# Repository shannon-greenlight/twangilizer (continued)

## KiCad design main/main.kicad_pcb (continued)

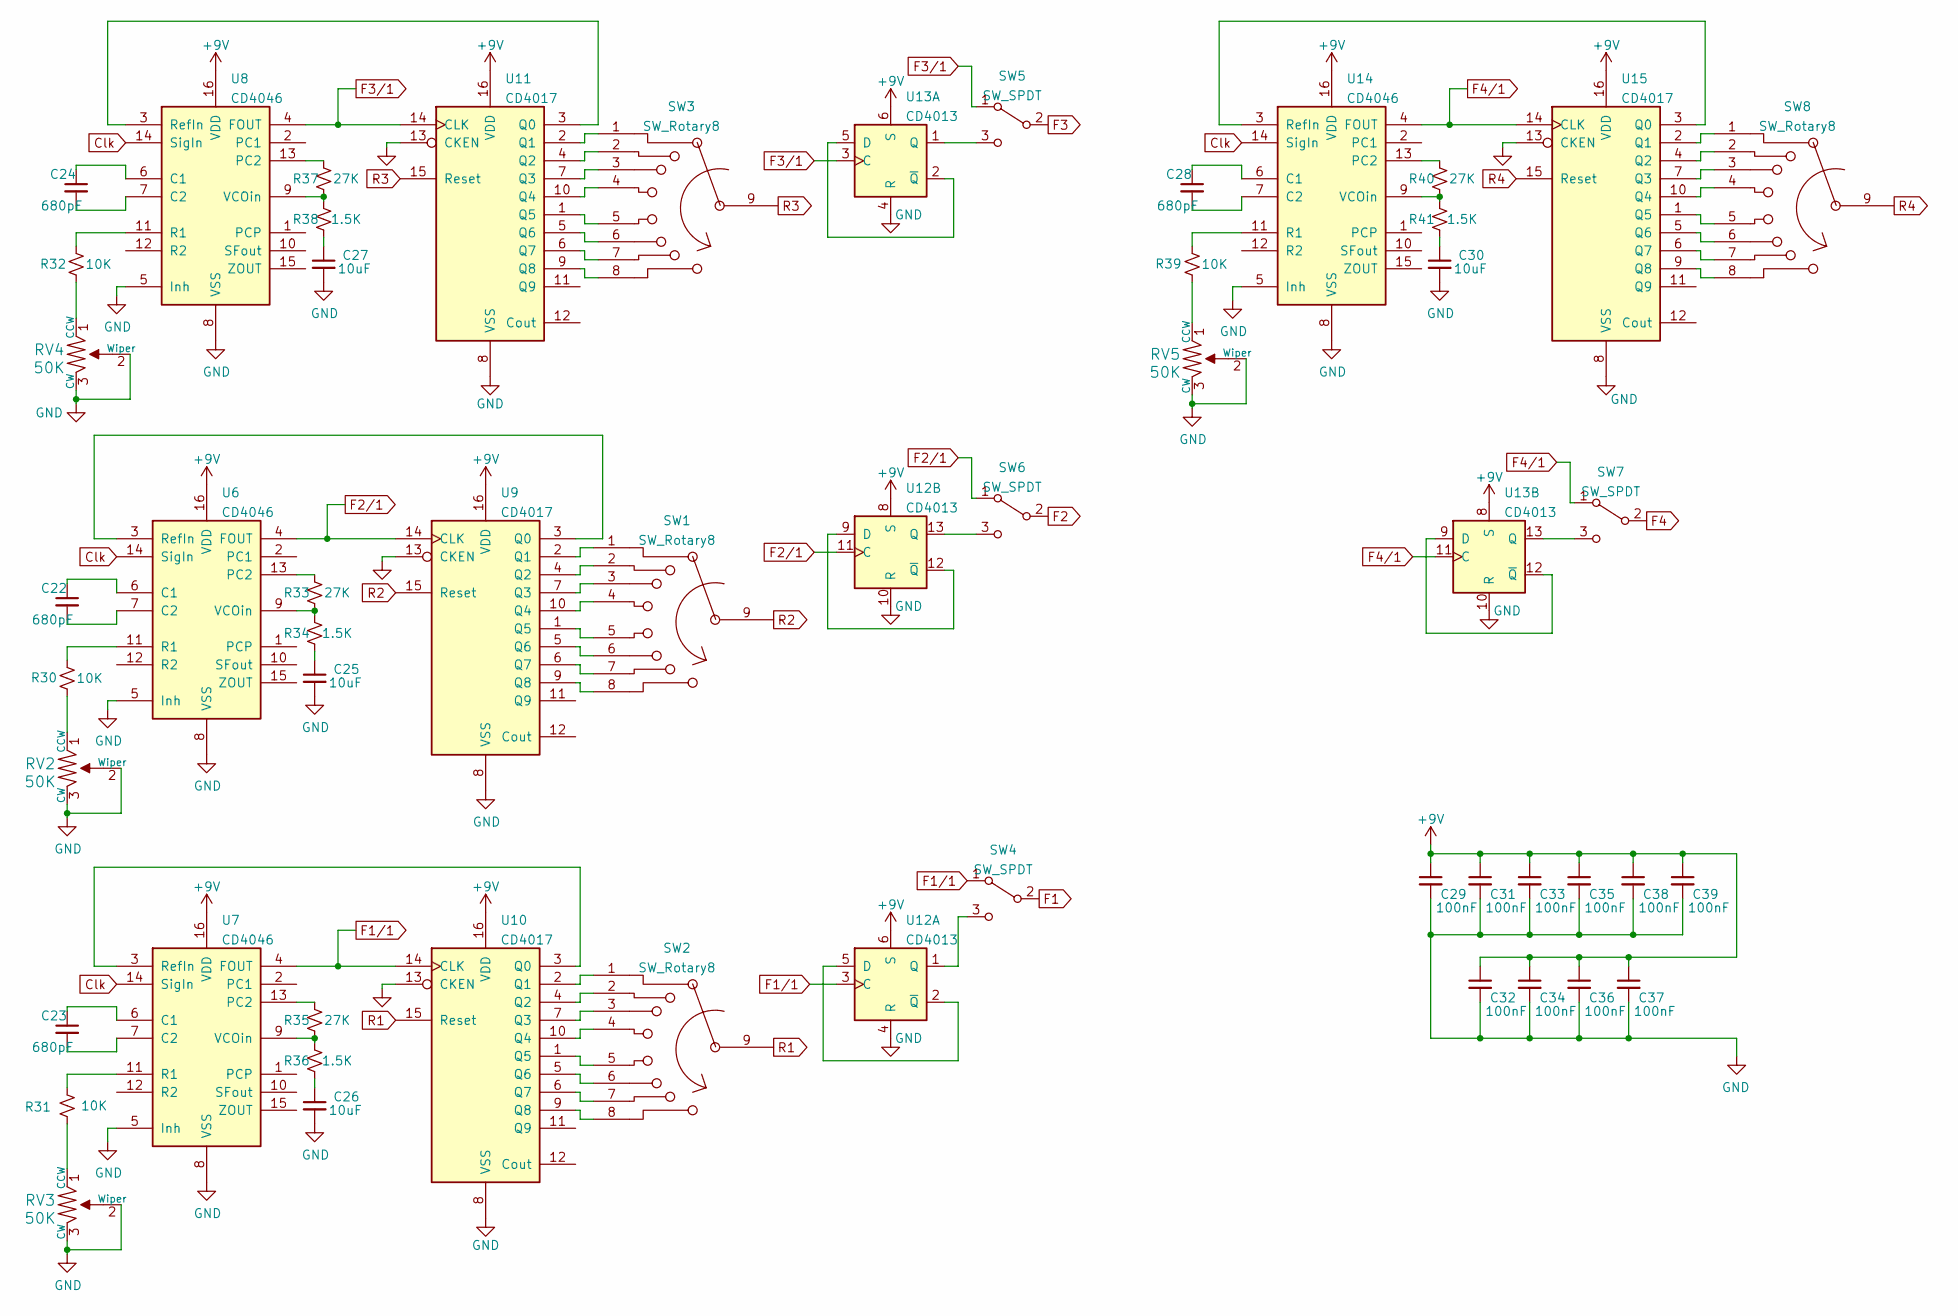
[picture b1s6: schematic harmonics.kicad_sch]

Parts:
C22, C23, C24, C28: 680pF; C_0805_2012Metric_Pad1.18x1.45mm_HandSolder; Digi-Key Part BC2662CT-ND
C25, C26, C27, C30: 10uF; C_0805_2012Metric_Pad1.18x1.45mm_HandSolder; Digi-Key Part 478-10836-1-ND
C29, C31, C32, C33, C34, C35, C36, C37, C38, C39: 100nF; C_0805_2012Metric_Pad1.18x1.45mm_HandSolder; Digi-Key Part 478-10836-1-ND
R30, R31, R32, R39: 10K; R_0603_1608Metric; Digi-Key Part CF14JT10K0CT-ND
R33, R35, R37, R40: 27K; R_0805_2012Metric_Pad1.20x1.40mm_HandSolder; Digi-Key Part CF14JT10K0CT-ND
R34, R36, R38, R41: 1.5K; R_0805_2012Metric_Pad1.20x1.40mm_HandSolder; Digi-Key Part CF14JT10K0CT-ND
RV2, RV3, RV4, RV5: 50K; Potentiometer_Bourns_3224W_Vertical; Digi-Key Part 490-2881-ND
SW1, SW2, SW3, SW8: SW_Rotary8; CPA_8; Digi-Key Part 1528-2925-ND
SW4, SW5, SW6, SW7: SW_SPDT; Toggle_Switch_100SP1T1B4M2QE; Digi-Key Part 2449-ANT11SF1CQE-ND
U6, U7, U8, U14: CD4046; TSSOP-16_4.4x5mm_P0.65mm; LCSC Part # C2651240
U9, U10, U11, U15: CD4017; SOIC-16_3.9x9.9mm_P1.27mm; Digi-Key Part 296-12808-1-ND
U12, U13: CD4013; SOIC-14_3.9x8.7mm_P1.27mm; LCSC Part # C13527

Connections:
+9V: C29.1, C31.1, C32.1, C33.1, C34.1, C35.1, C36.1, C37.1, C38.1, C39.1, U6.16 (VDD), U7.16 (VDD), U8.16 (VDD), U9.16 (VDD), U10.16 (VDD), U11.16 (VDD), U12.6 (S), U12.8 (S), U13.6 (S), U13.8 (S), U14.16 (VDD), U15.16 (VDD); also elsewhere on the board
Clk: U6.14 (SigIn), U7.14 (SigIn), U8.14 (SigIn), U14.14 (SigIn); also elsewhere on the board
F1: SW4.2 (B); also elsewhere on the board
F1/1: SW4.1 (A), U7.4 (FOUT), U10.14 (CLK), U12.3 (C)
F2: SW6.2 (B); also elsewhere on the board
F2/1: SW6.1 (A), U6.4 (FOUT), U9.14 (CLK), U12.11 (C)
F3: SW5.2 (B); also elsewhere on the board
F3/1: SW5.1 (A), U8.4 (FOUT), U11.14 (CLK), U13.3 (C)
F4: SW7.2 (B); also elsewhere on the board
F4/1: SW7.1 (A), U13.11 (C), U14.4 (FOUT), U15.14 (CLK)
GND: C25.2, C26.2, C27.2, C29.2, C30.2, C31.2, C32.2, C33.2, C34.2, C35.2, C36.2, C37.2, C38.2, C39.2, RV2.2 (Wiper), RV2.3 (CW), RV3.2 (Wiper), RV3.3 (CW), RV4.2 (Wiper), RV4.3 (CW), RV5.2 (Wiper), RV5.3 (CW), U6.5 (Inh), U6.8 (VSS), U7.5 (Inh), U7.8 (VSS), U8.5 (Inh), U8.8 (VSS), U9.8 (VSS), U9.13 (CKEN), U10.8 (VSS), U10.13 (CKEN), U11.8 (VSS), U11.13 (CKEN), U12.4 (R), U12.10 (R), U13.4 (R), U13.10 (R), U14.5 (Inh), U14.8 (VSS), U15.8 (VSS), U15.13 (CKEN); also elsewhere on the board
unnamed: C22.1, U6.6 (C1)
unnamed: C22.2, U6.7 (C2)
unnamed: C23.1, U7.6 (C1)
unnamed: C23.2, U7.7 (C2)
unnamed: C24.1, U8.6 (C1)
unnamed: C24.2, U8.7 (C2)
unnamed: C25.1, R34.2
unnamed: C26.1, R36.2
unnamed: C27.1, R38.2
unnamed: C28.1, U14.6 (C1)
unnamed: C28.2, U14.7 (C2)
unnamed: C30.1, R41.2
unnamed: R30.1, U6.11 (R1)
unnamed: R30.2, RV2.1 (CCW)
unnamed: R31.1, U7.11 (R1)
unnamed: R31.2, RV3.1 (CCW)
unnamed: R32.1, U8.11 (R1)
unnamed: R32.2, RV4.1 (CCW)
unnamed: R33.1, U6.13 (PC2)
unnamed: R33.2, R34.1, U6.9 (VCOin)
unnamed: R35.1, U7.13 (PC2)
unnamed: R35.2, R36.1, U7.9 (VCOin)
unnamed: R37.1, U8.13 (PC2)
unnamed: R37.2, R38.1, U8.9 (VCOin)
unnamed: R39.1, U14.11 (R1)
unnamed: R39.2, RV5.1 (CCW)
unnamed: R40.1, U14.13 (PC2)
unnamed: R40.2, R41.1, U14.9 (VCOin)
unnamed: SW1.1, U9.2 (Q1)
unnamed: SW1.2, U9.4 (Q2)
unnamed: SW1.3, U9.7 (Q3)
unnamed: SW1.4, U9.10 (Q4)
unnamed: SW1.5, U9.1 (Q5)
unnamed: SW1.6, U9.5 (Q6)
unnamed: SW1.7, U9.6 (Q7)
unnamed: SW1.8, U9.9 (Q8)
unnamed: SW2.1, U10.2 (Q1)
unnamed: SW2.2, U10.4 (Q2)
unnamed: SW2.3, U10.7 (Q3)
unnamed: SW2.4, U10.10 (Q4)
unnamed: SW2.5, U10.1 (Q5)
unnamed: SW2.6, U10.5 (Q6)
unnamed: SW2.7, U10.6 (Q7)
unnamed: SW2.8, U10.9 (Q8)
unnamed: SW3.1, U11.2 (Q1)
unnamed: SW3.2, U11.4 (Q2)
unnamed: SW3.3, U11.7 (Q3)
unnamed: SW3.4, U11.10 (Q4)
unnamed: SW3.5, U11.1 (Q5)
unnamed: SW3.6, U11.5 (Q6)
unnamed: SW3.7, U11.6 (Q7)
unnamed: SW3.8, U11.9 (Q8)
unnamed: SW4.3 (C), U12.1 (Q)
unnamed: SW5.3 (C), U13.1 (Q)
unnamed: SW6.3 (C), U12.13 (Q)
unnamed: SW7.3 (C), U13.13 (Q)
unnamed: SW8.1, U15.2 (Q1)
unnamed: SW8.2, U15.4 (Q2)
unnamed: SW8.3, U15.7 (Q3)
unnamed: SW8.4, U15.10 (Q4)
unnamed: SW8.5, U15.1 (Q5)
unnamed: SW8.6, U15.5 (Q6)
unnamed: SW8.7, U15.6 (Q7)
unnamed: SW8.8, U15.9 (Q8)
unnamed: U6.3 (RefIn), U9.3 (Q0)
unnamed: U7.3 (RefIn), U10.3 (Q0)
unnamed: U8.3 (RefIn), U11.3 (Q0)
unnamed: U12.2 (~Q), U12.5 (D)
unnamed: U12.9 (D), U12.12 (~Q)
unnamed: U13.2 (~Q), U13.5 (D)
unnamed: U13.9 (D), U13.12 (~Q)
unnamed: U14.3 (RefIn), U15.3 (Q0)
R1: SW2.9, U10.15 (Reset)
R2: SW1.9, U9.15 (Reset)
R3: SW3.9, U11.15 (Reset)
R4: SW8.9, U15.15 (Reset)

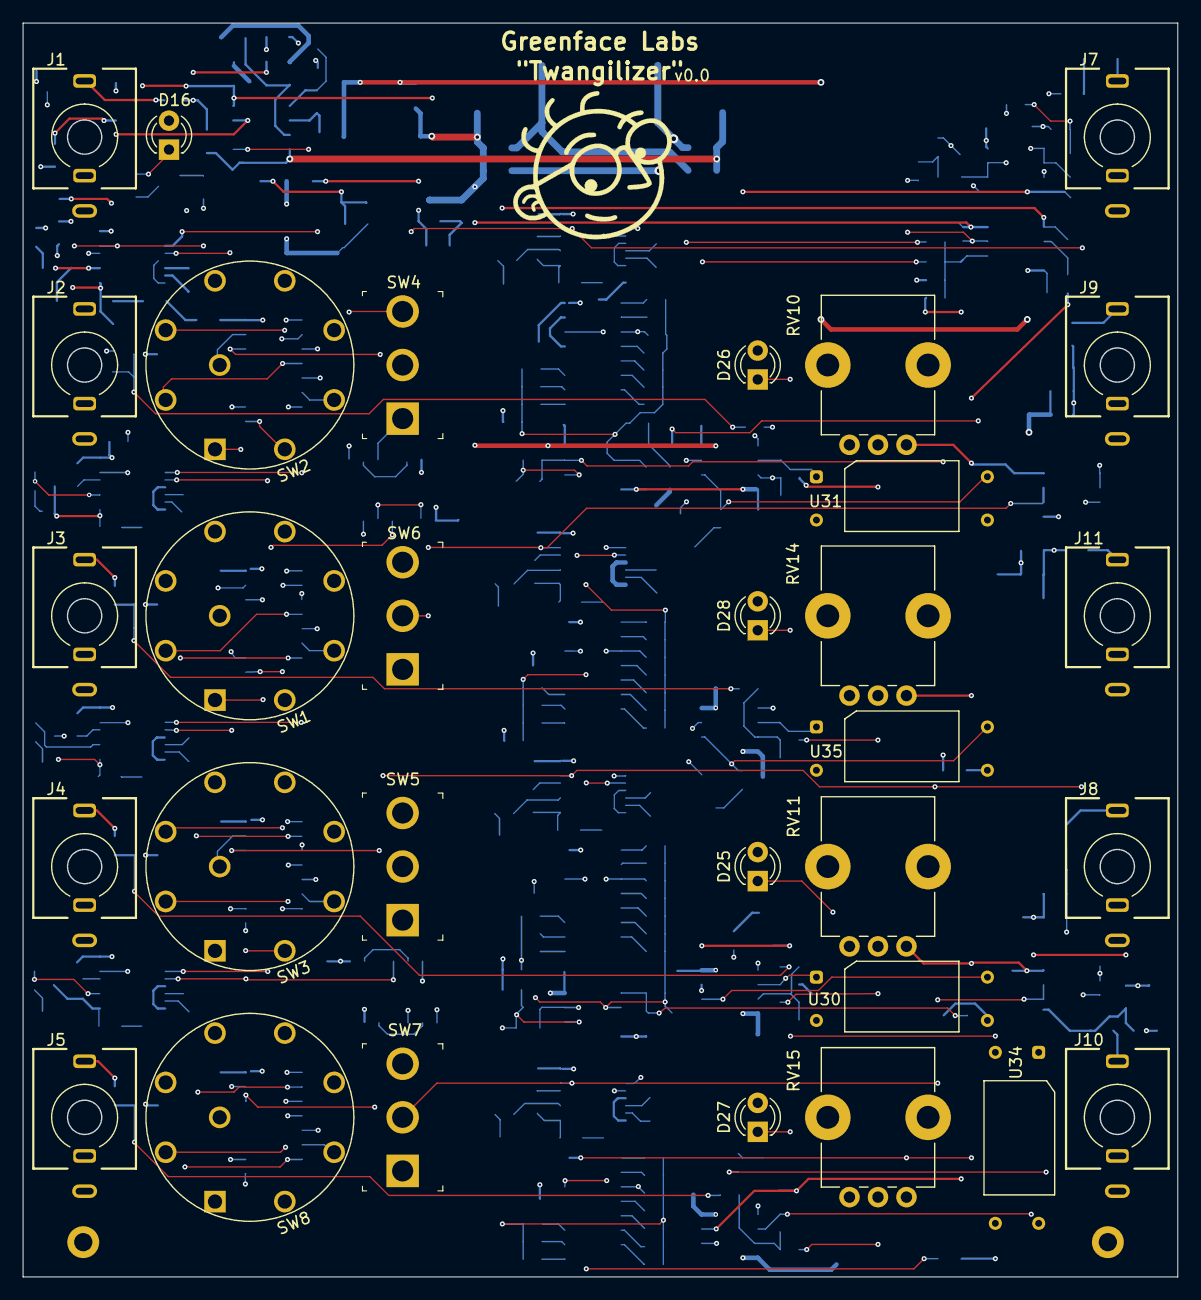
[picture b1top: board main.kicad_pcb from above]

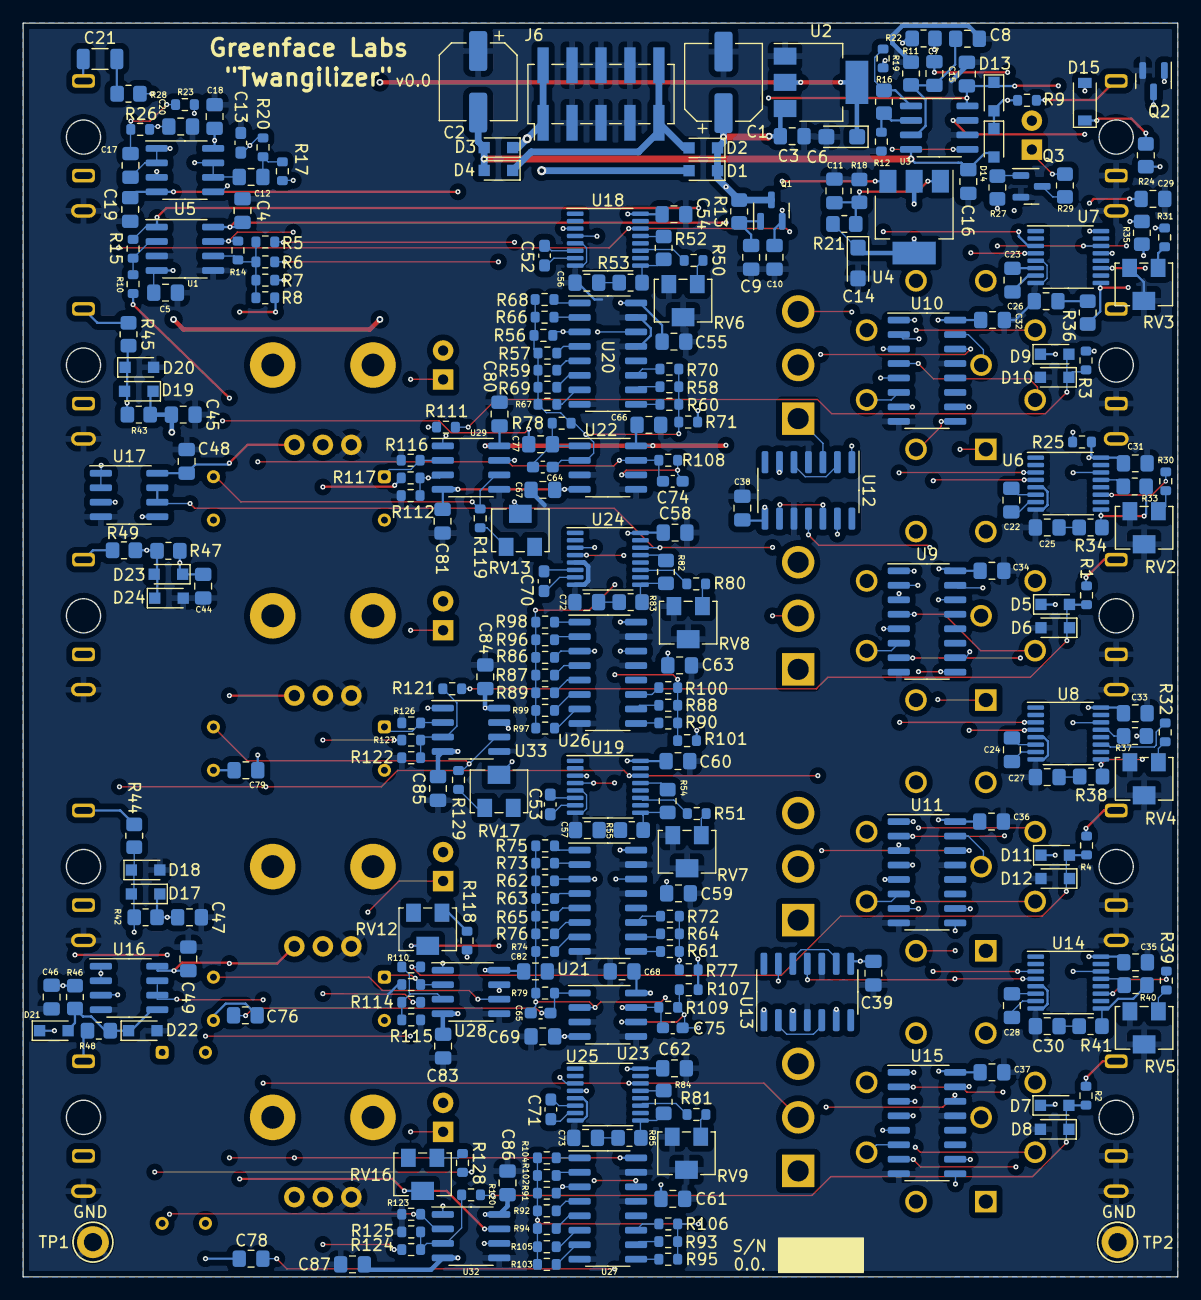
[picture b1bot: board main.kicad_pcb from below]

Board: 4 copper layers, 101.2 x 109.9 mm, 314 parts (282 on the bottom side), 251 nets.

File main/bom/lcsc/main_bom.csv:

"Designator","Comment","Footprint","JLCPCBPart#"
"C1, C2, ","100uF","Capacitor_SMD:CP_Elec_6.3x5.4_Nichicon","C2887272"
"C3, C4, C5, C7, C9, C10, C15, C16, C18, C19, C29, C31, C32, C33, C34, C35, C36, C37, C38, C39, C44, C45, C46, C47, C48, C49, C54, C55, C58, C59, C60, C61, C62, C63, C66, C67, C68, C69, C80, C81, C82, C83, C84, C85, C86, C87, ","100nF","Capacitor_SMD:C_0805_2012Metric_Pad1.18x1.45mm_HandSolder","C49678"
"C6, C14, ","22uF","Capacitor_Tantalum_SMD:CP_EIA-3216-18_Kemet-A","C129272"
"C8, C17, ","1nF","Capacitor_SMD:C_0805_2012Metric_Pad1.18x1.45mm_HandSolder","C46653"
"C11, C25, C26, C27, C30, C56, C57, C72, C73, ","10uF","Capacitor_SMD:C_0805_2012Metric_Pad1.18x1.45mm_HandSolder","C15850"
"C12, C20, ","100pF","Capacitor_SMD:C_0805_2012Metric_Pad1.18x1.45mm_HandSolder","C1790"
"C13, ","10pF","Capacitor_SMD:C_0603_1608Metric_Pad1.08x0.95mm_HandSolder","C1634"
"C21, ","4.7uF","Capacitor_SMD:C_1206_3216Metric","C29823"
"C22, C23, C24, C28, ","680pF","Capacitor_SMD:C_0805_2012Metric_Pad1.18x1.45mm_HandSolder","C384742"
"C52, C53, C70, C71, ","300p","Capacitor_SMD:C_0603_1608Metric_Pad1.08x0.95mm_HandSolder","C519401"
"C64, C65, C74, C75, ","30p","Capacitor_SMD:C_0603_1608Metric_Pad1.08x0.95mm_HandSolder","C1658"
"C76, C77, C78, C79, ","22uF","Capacitor_SMD:C_0805_2012Metric_Pad1.18x1.45mm_HandSolder","C45783"
"D1, D2, D3, D4, D5, D6, D7, D8, D9, D10, D11, D12, D13, D14, D17, D18, D19, D20, D21, D22, D23, D24, ","1N5819","Diode_SMD:D_SOD-323_HandSoldering","C191023"
"D15, ","1N4148","Diode_SMD:D_SOD-123","C81598"
"J6, ","2x5 Header","Connector_PinHeader_2.54mm:PinHeader_2x05_P2.54mm_Vertical_SMD","C124391"
"Q1, Q2, Q3, ","MMBT3904","Package_TO_SOT_SMD:SOT-23","C20526"
"R1, R2, R3, R4, R5, R6, R7, R8, R9, R10, R14, R15, R19, R30, R31, R32, R39, R50, R51, R80, R81, ","10K","Resistor_SMD:R_0603_1608Metric","C25804"
"R11, R16, ","100K","Resistor_SMD:R_0805_2012Metric_Pad1.20x1.40mm_HandSolder","C149504"
"R12, R25, ","2K","Resistor_SMD:R_0603_1608Metric","C22975"
"R13, R24, R27, ","68K","Resistor_SMD:R_0805_2012Metric_Pad1.20x1.40mm_HandSolder","C17801"
"R17, ","133K","Resistor_SMD:R_0603_1608Metric","C321714"
"R18, ","3.83K","Resistor_SMD:R_0805_2012Metric_Pad1.20x1.40mm_HandSolder","C483108"
"R20, ","475K","Resistor_SMD:R_0603_1608Metric","C403244"
"R21, ","620","Resistor_SMD:R_0805_2012Metric_Pad1.20x1.40mm_HandSolder","C144551"
"R22, ","200K","Resistor_SMD:R_0805_2012Metric_Pad1.20x1.40mm_HandSolder","C17539"
"R23, ","4.42K","Resistor_SMD:R_0603_1608Metric","C23043"
"R26, ","143K","Resistor_SMD:R_0603_1608Metric","C304703"
"R28, R42, R43, R44, R45, R46, R47, R48, R49, ","510","Resistor_SMD:R_0805_2012Metric_Pad1.20x1.40mm_HandSolder","C2842425"
"R29, R33, R35, R37, R40, R52, R54, R82, R84, ","27K","Resistor_SMD:R_0805_2012Metric_Pad1.20x1.40mm_HandSolder","C17593"
"R34, R36, R38, R41, R53, R55, R83, R85, ","1.5K","Resistor_SMD:R_0805_2012Metric_Pad1.20x1.40mm_HandSolder","C4310"
"R56, R62, R86, R91, ","162K","Resistor_SMD:R_0603_1608Metric","C217756"
"R57, R63, R87, R92, ","154K","Resistor_SMD:R_0603_1608Metric","C321731"
"R58, R64, R88, R93, ","210K","Resistor_SMD:R_0603_1608Metric","C227705"
"R59, R65, R89, R94, ","300K","Resistor_SMD:R_0603_1608Metric","C23024"
"R60, R61, R90, R95, ","237K","Resistor_SMD:R_0603_1608Metric","C403089"
"R66, R73, R96, R102, ","150K","Resistor_SMD:R_0603_1608Metric","C22807"
"R67, R74, R97, R103, ","174K","Resistor_SMD:R_0603_1608Metric","C2933159"
"R68, R75, R98, R104, ","261K","Resistor_SMD:R_0603_1608Metric","C2930083"
"R69, R76, R99, R105, ","287K","Resistor_SMD:R_0603_1608Metric","C5159700"
"R70, R72, R100, R106, ","191K","Resistor_SMD:R_0603_1608Metric","C861179"
"R71, R77, R101, R107, R110, R111, R112, R115, R120, R121, R122, R125, ","200K","Resistor_SMD:R_0603_1608Metric","C25811"
"R78, R79, R108, R109, ","332K","Resistor_SMD:R_0603_1608Metric","C403165"
"R113, R116, R123, R126, ","20K","Resistor_SMD:R_0603_1608Metric","C4184"
"R114, R117, R124, R127, ","180K","Resistor_SMD:R_0603_1608Metric","C3016400"
"R118, R119, R128, R129, ","430","Resistor_SMD:R_0603_1608Metric","C23170"
"RV2, RV3, RV4, RV5, RV6, RV7, RV8, RV9, ","50K","sputterizer:Potentiometer_Bourns_3224W_Vertical","C48484"
"RV12, RV13, RV16, RV17, ","500","Potentiometer_SMD:Potentiometer_Bourns_3224W_Vertical","C116324"
"TP1, TP2, ","TestPoint","TestPoint:TestPoint_Keystone_5005-5009_Compact","C5199801"
"U1, U3, U5, U22, U23, U28, U29, U32, U33, ","TL072CP","Package_SO:SOIC-8_3.9x4.9mm_P1.27mm","C6961"
"U2, ","AMS1117-5.0","Package_TO_SOT_SMD:SOT-223-3_TabPin2","C6187"
"U4, ","LM317_SOT-223","Package_TO_SOT_SMD:SOT-223-3_TabPin2","C347367"
"U6, U7, U8, U14, U18, U19, U24, U25, ","CD4046","Package_SO:TSSOP-16_4.4x5mm_P0.65mm","C2651240"
"U9, U10, U11, U15, U20, U21, U26, U27, ","CD4017","Package_SO:SOIC-16_3.9x9.9mm_P1.27mm","C356694"
"U12, U13, ","CD4013","Package_SO:SOIC-14_3.9x8.7mm_P1.27mm","C13527"
"U16, U17, ","CD40107","Package_SO:SOIC-8_3.9x4.9mm_P1.27mm","C2691402"

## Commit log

2024-01-17 Init checkin
2024-01-18 Removed
2024-01-18 Switched PLL cap to 680p
2024-01-20 Switch to Thonk jacks.
    Reduces use of extended parts.
2024-02-06 Version 1.0
2024-02-06 The real v1.0
2024-02-21 v1.0
    Docs still need work.
    Oscillators.sch not used. Saved just in case.
2024-03-03 Work in progress
    Adds User Manual
    Changes CV range to 0 - 8V
    Adds spice vactrol test circuit.
    Adds VCA spice study
    Updates other spice and excel files.
2024-03-14 Create CLK Pickoff.xlsx
    Resistor planner
2024-03-14 Latest gain plan.
    Version 1.1
    Sent to JLCPCB
2024-04-28 Version 1.2
2024-05-06 Attempt to improve sine wave approximation graph.
2025-02-21 v2.0
